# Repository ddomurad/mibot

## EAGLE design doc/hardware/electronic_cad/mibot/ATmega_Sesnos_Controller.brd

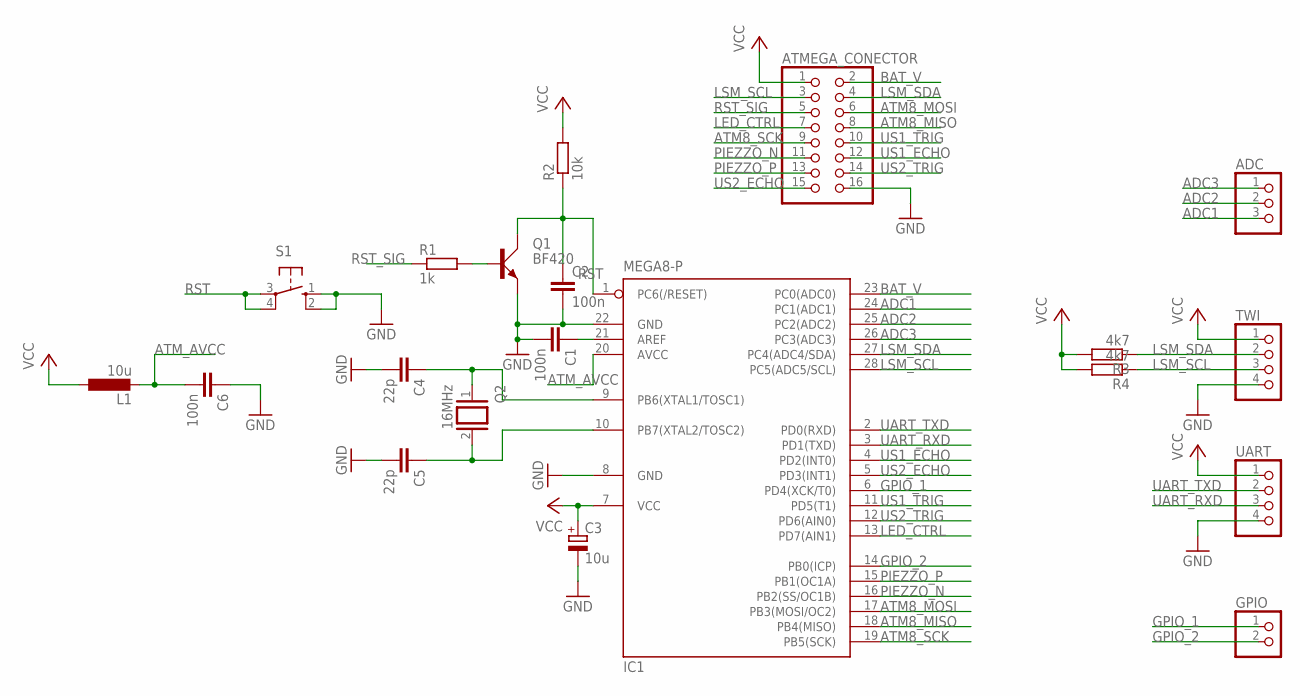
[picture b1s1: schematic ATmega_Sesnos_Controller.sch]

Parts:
ADC: PINHD-1X3/90; 1X03/90
ATMEGA_CONECTOR: PINHD-2X8; 2X08
C1, C2, C6: 100n; C025-024X044
C3: 10u; E5-5
C4, C5: 22p; C025-024X044
GPIO: PINHD-1X2/90; 1X02/90
IC1: MEGA8-P; DIL28-3
L1: 10u; 0204/7
Q1: BF420; SOT54D
Q2: 16MHz; QS
R1: 1k; 0309/10
R2: 10k; 0309/10
R3, R4: 4k7; 0204/5
S1: 10-XX; B3F-10XX
TWI: PINHD-1X4/90; 1X04/90
UART: PINHD-1X4/90; 1X04/90

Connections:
ADC1: ADC.3, IC1.24 (PC1(ADC1))
ADC2: ADC.2, IC1.25 (PC2(ADC2))
ADC3: ADC.1, IC1.26 (PC3(ADC3))
ATM8_MISO: ATMEGA_CONECTOR.8, IC1.18 (PB4(MISO))
ATM8_MOSI: ATMEGA_CONECTOR.6, IC1.17 (PB3(MOSI/OC2))
ATM8_SCK: ATMEGA_CONECTOR.9, IC1.19 (PB5(SCK))
ATM_AVCC: C6.2, IC1.20 (AVCC), L1.2
BAT_V: ATMEGA_CONECTOR.2, IC1.23 (PC0(ADC0))
GND: ATMEGA_CONECTOR.16, C1.2, C2.2, C3.-, C4.2, C5.2, C6.1, IC1.8 (GND), IC1.22 (GND), Q1.E, S1.1 (S), S1.2 (S1), TWI.4, UART.4
GPIO_1: GPIO.1, IC1.6 (PD4(XCK/T0))
GPIO_2: GPIO.2, IC1.14 (PB0(ICP))
LED_CTRL: ATMEGA_CONECTOR.7, IC1.13 (PD7(AIN1))
LSM_SCL: ATMEGA_CONECTOR.3, IC1.28 (PC5(ADC5/SCL)), R4.1, TWI.3
LSM_SDA: ATMEGA_CONECTOR.4, IC1.27 (PC4(ADC4/SDA)), R3.1, TWI.2
unnamed: C1.1, IC1.21 (AREF)
unnamed: C4.1, IC1.9 (PB6(XTAL1/TOSC1)), Q2.1
unnamed: C5.1, IC1.10 (PB7(XTAL2/TOSC2)), Q2.2
unnamed: Q1.B, R1.2
PIEZZO_N: ATMEGA_CONECTOR.11, IC1.16 (PB2(SS/OC1B))
PIEZZO_P: ATMEGA_CONECTOR.13, IC1.15 (PB1(OC1A))
RST: C2.1, IC1.1 (PC6(/RESET)), Q1.C, R2.1, S1.3, S1.4 (P1)
RST_SIG: ATMEGA_CONECTOR.5, R1.1
UART_RXD: IC1.3 (PD1(TXD)), UART.3
UART_TXD: IC1.2 (PD0(RXD)), UART.2
US1_ECHO: ATMEGA_CONECTOR.12, IC1.4 (PD2(INT0))
US1_TRIG: ATMEGA_CONECTOR.10, IC1.11 (PD5(T1))
US2_ECHO: ATMEGA_CONECTOR.15, IC1.5 (PD3(INT1))
US2_TRIG: ATMEGA_CONECTOR.14, IC1.12 (PD6(AIN0))
VCC: ATMEGA_CONECTOR.1, C3.+, IC1.7 (VCC), L1.1, R2.2, R3.2, R4.2, TWI.1, UART.1

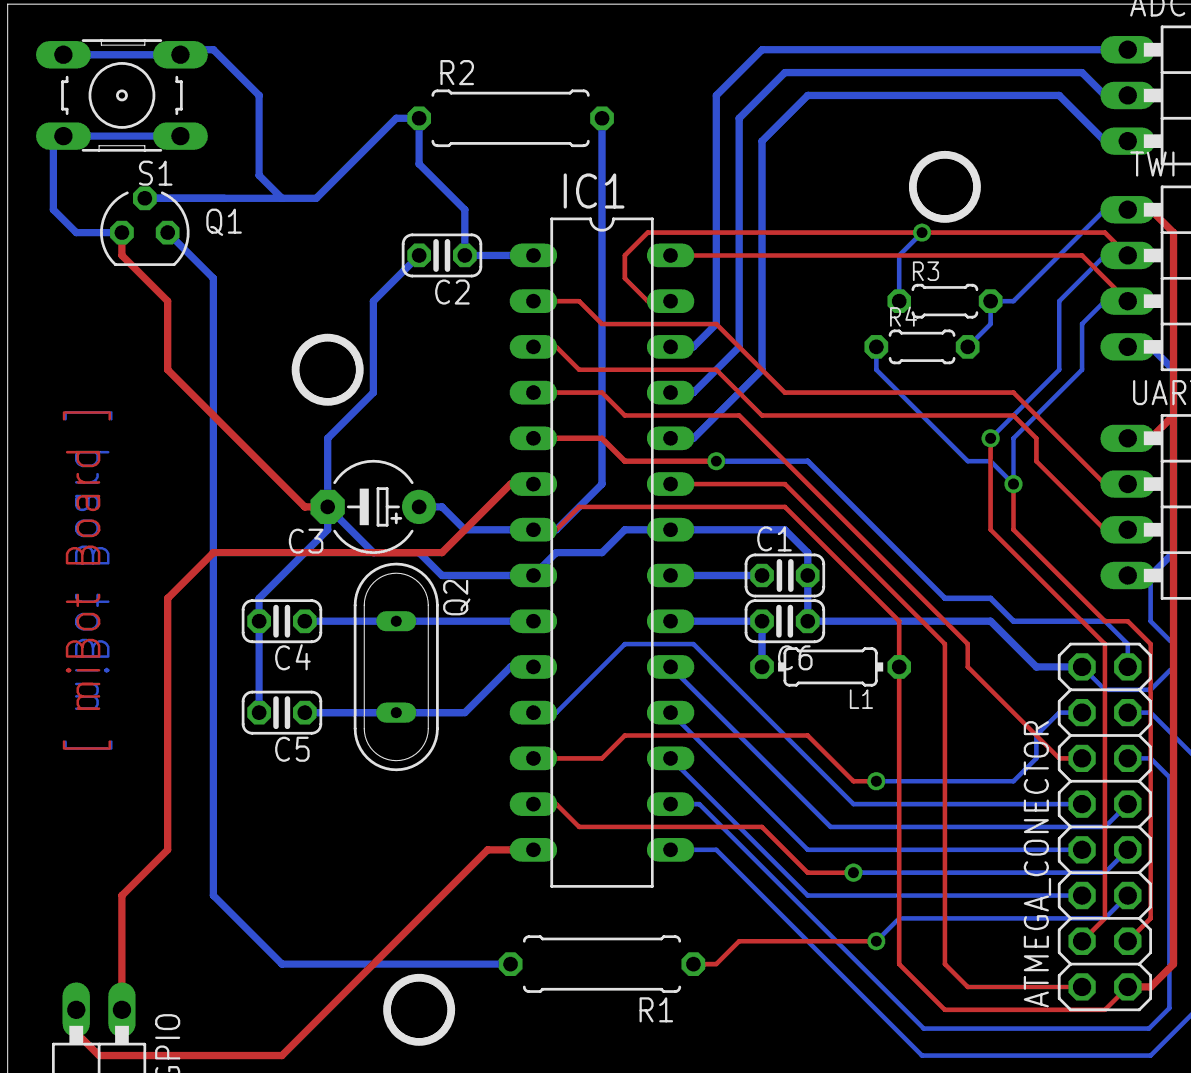
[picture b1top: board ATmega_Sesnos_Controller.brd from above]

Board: 2 copper layers, 20 parts (0 on the bottom side), 29 nets.

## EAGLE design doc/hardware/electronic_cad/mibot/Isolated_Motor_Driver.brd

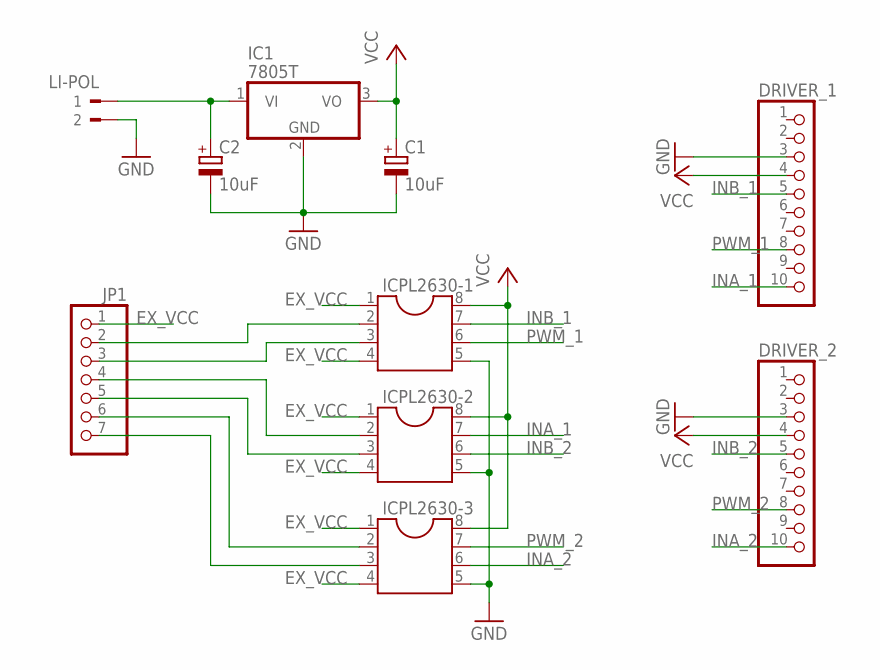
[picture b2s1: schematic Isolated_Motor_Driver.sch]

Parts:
C1, C2: 10uF; E5-5
DRIVER_1, DRIVER_2: PINHD-1X10; 1X10
IC1: 7805T; TO220H
ICPL2630-1, ICPL2630-2, ICPL2630-3: DIL8S; SOCKET-08
JP1: PINHD-1X7; 1X07
LI-POL: 90-2

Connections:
EX_INA_1: ICPL2630-1.2, JP1.2
EX_INA_2: ICPL2630-2.3, JP1.5
EX_INB_1: ICPL2630-1.3, JP1.3
EX_INB_2: ICPL2630-3.2, JP1.6
EX_PWM_1: ICPL2630-2.2, JP1.4
EX_PWM_2: ICPL2630-3.3, JP1.7
EX_VCC: ICPL2630-1.1, ICPL2630-1.4, ICPL2630-2.1, ICPL2630-2.4, ICPL2630-3.1, ICPL2630-3.4, JP1.1
GND: C1.-, C2.-, DRIVER_1.3, DRIVER_2.3, IC1.2 (GND), ICPL2630-1.5, ICPL2630-2.5, ICPL2630-3.5, LI-POL.2
INA_1: DRIVER_1.10, ICPL2630-2.7
INA_2: DRIVER_2.10, ICPL2630-3.6
INB_1: DRIVER_1.5, ICPL2630-1.7
INB_2: DRIVER_2.5, ICPL2630-2.6
unnamed: C2.+, IC1.1 (VI), LI-POL.1
PWM_1: DRIVER_1.8, ICPL2630-1.6
PWM_2: DRIVER_2.8, ICPL2630-3.7
VCC: C1.+, DRIVER_1.4, DRIVER_2.4, IC1.3 (VO), ICPL2630-1.8, ICPL2630-2.8, ICPL2630-3.8

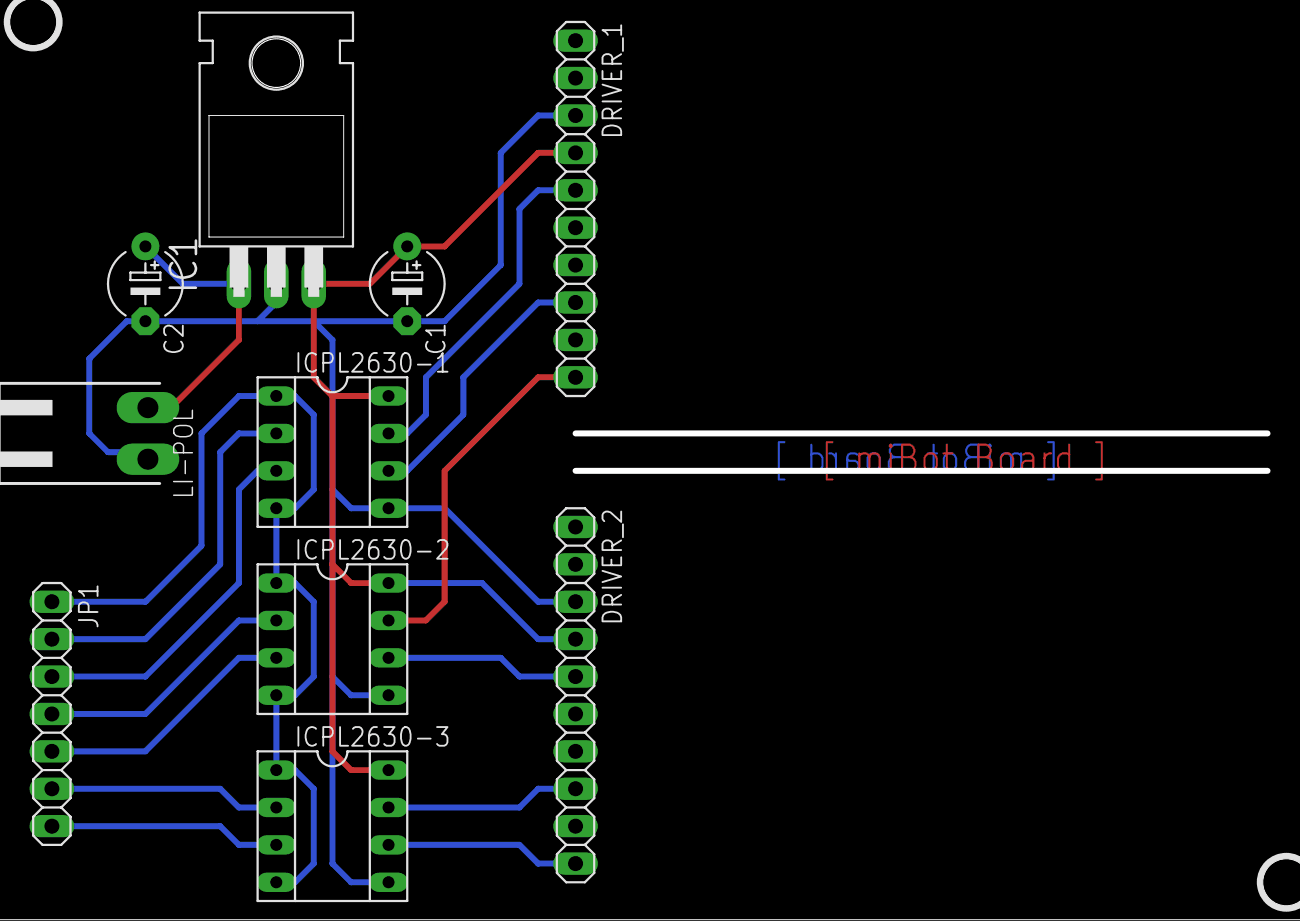
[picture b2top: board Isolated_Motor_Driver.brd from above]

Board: 2 copper layers, 10 parts (0 on the bottom side), 16 nets.

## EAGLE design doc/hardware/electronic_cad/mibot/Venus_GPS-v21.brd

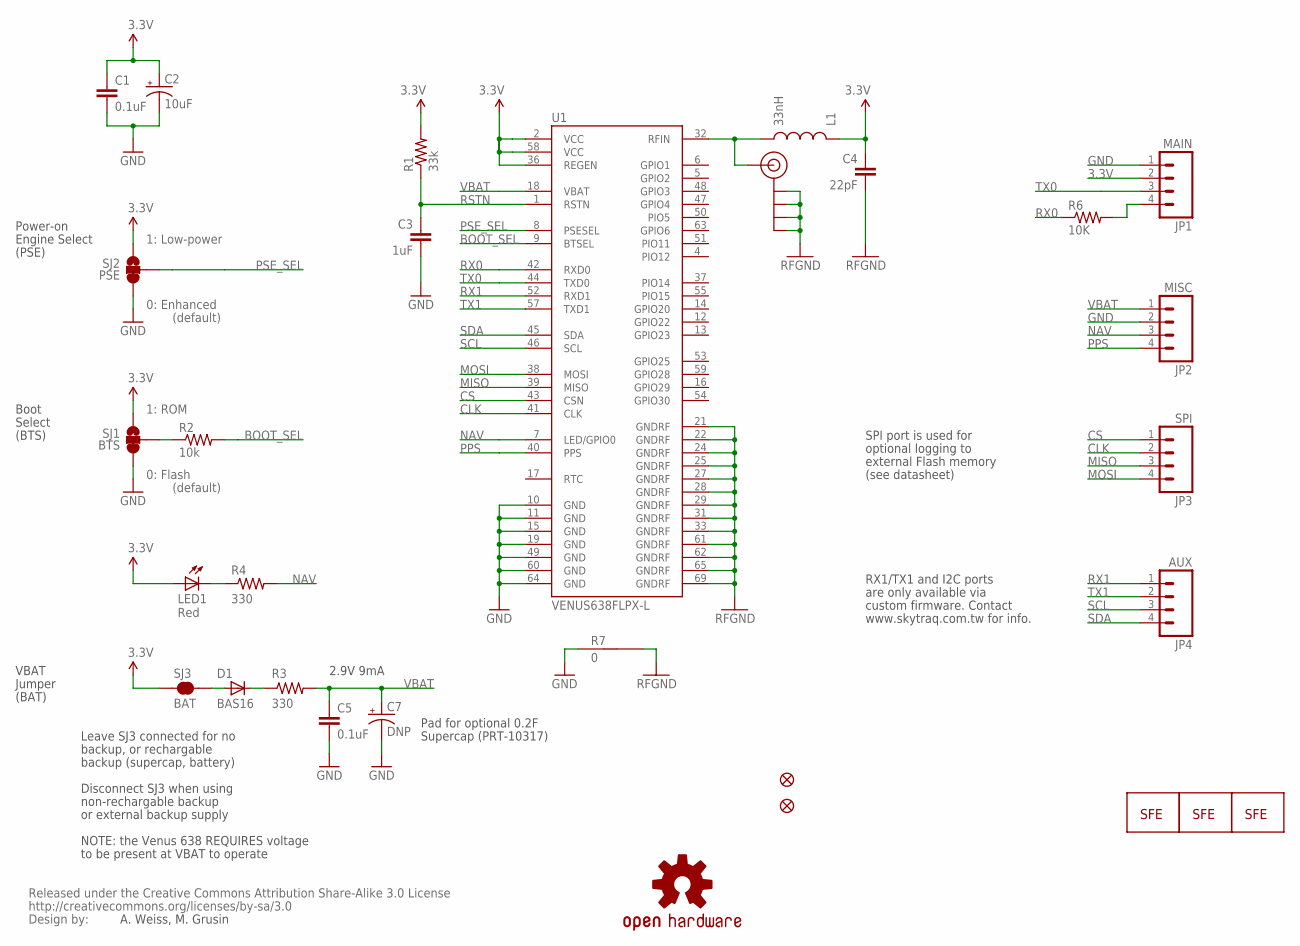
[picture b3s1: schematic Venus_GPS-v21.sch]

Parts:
C1, C5: 0.1uF; 0402-CAP
C2: 10uF; EIA3216
C3: 1uF; 0402-CAP
C4: 22pF; 0402-CAP
C7: DNP; EN_J2
D1: BAS16; SOD-323
JP1: MAIN; 1X04
JP2: MISC; 1X04
JP3: SPI; 1X04
JP4: AUX; 1X04
JP5: SMA_EDGE; SMA-EDGE
JP6, JP7: FIDUCIALUFIDUCIAL; MICRO-FIDUCIAL
L1: 33nH; C0402
LED1: Red; LED-0603
LOGO1, LOGO2: LOGO-SFESK; SFE-LOGO-FLAME
LOGO3: LOGO-SFENW2; SFE-NEW-WEB
R1: 33k; 0402-RES
R2: 10k; 0402-RES
R3, R4: 330; 0402-RES
R6: 10K; 0402-RES
R7: 0; GND-JUMP
SJ1: BTS; SJ_3_PASTE2&3
SJ2: PSE; SJ_3_PASTE2&3
SJ3: BAT; SJ_2S
U1: VENUS638FLPX-L; VENUS638FLPX
U$4: OSHW-LOGOS; OSHW-LOGO-S
U$5: CREATIVE_COMMONS

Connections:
3.3V: C1.1, C2.A (+), C4.1, JP1.2, L1.1, LED1.A, R1.2, SJ1.1, SJ2.1, SJ3.1, U1.2 (VCC), U1.36 (REGEN), U1.58 (VCC)
ANT: JP5.SIG (SIGNAL), L1.2, U1.32 (RFIN)
BOOT_SEL: R2.2, U1.9 (BTSEL)
CLK: JP3.2, U1.41 (CLK)
CS: JP3.1, U1.43 (CSN)
GND: C1.2, C2.C (-), C3.2, C5.2, C7.-, JP1.1, JP2.2, R7.1, SJ1.3, SJ2.3, U1.10 (GND), U1.11 (GND), U1.15 (GND), U1.19 (GND), U1.49 (GND), U1.60 (GND), U1.64 (GND)
MISO: JP3.3, U1.39 (MISO)
MOSI: JP3.4, U1.38 (MOSI)
unnamed: LED1.C, R4.1
unnamed: R2.1, SJ1.2
unnamed: D1.1 (C), R3.1
unnamed: D1.2 (A), SJ3.2
NAV: JP2.3, R4.2, U1.7 (LED/GPIO0)
PPS: JP2.4, U1.40 (PPS)
PSE_SEL: SJ2.2, U1.8 (PSESEL)
RFGND: C4.2, JP5.GND@0 (GND), JP5.GND@1 (GND), JP5.GND@2 (GND), JP5.GND@3 (GND), R7.2, U1.21 (GNDRF), U1.22 (GNDRF), U1.24 (GNDRF), U1.25 (GNDRF), U1.27 (GNDRF), U1.28 (GNDRF), U1.29 (GNDRF), U1.31 (GNDRF), U1.33 (GNDRF), U1.61 (GNDRF), U1.62 (GNDRF), U1.65 (GNDRF), U1.69 (GNDRF)
RSTN: C3.1, R1.1, U1.1 (RSTN)
RX0: R6.1, U1.42 (RXD0)
RX1: JP4.1, U1.52 (RXD1)
RX01: JP1.4, R6.2
SCL: JP4.3, U1.46 (SCL)
SDA: JP4.4, U1.45 (SDA)
TX0: JP1.3, U1.44 (TXD0)
TX1: JP4.2, U1.57 (TXD1)
VBAT: C5.1, C7.+, JP2.1, R3.2, U1.18 (VBAT)

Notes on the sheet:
RFGND
1: Low-power
0: Enhanced
0: Flash
1: ROM
(default)
A. Weiss, M. Grusin
Supercap (PRT-10317)
Pad for optional 0.2F
2.9V 9mA
RX1/TX1 and I2C ports
are only available via
SPI port is used for
optional logging to
external Flash memory
(see datasheet)
custom firmware. Contact
www.skytraq.com.tw for info.
Power-on
Engine Select
Boot
Select
(PSE)
(BTS)
VBAT
Jumper
(BAT)
Leave SJ3 connected for no
backup, or rechargable
backup (supercap, battery)
Disconnect SJ3 when using
non-rechargable backup
or external backup supply
NOTE: the Venus 638 REQUIRES voltage
to be present at VBAT to operate

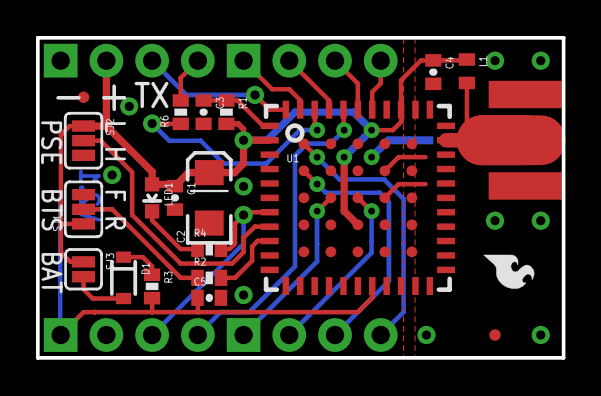
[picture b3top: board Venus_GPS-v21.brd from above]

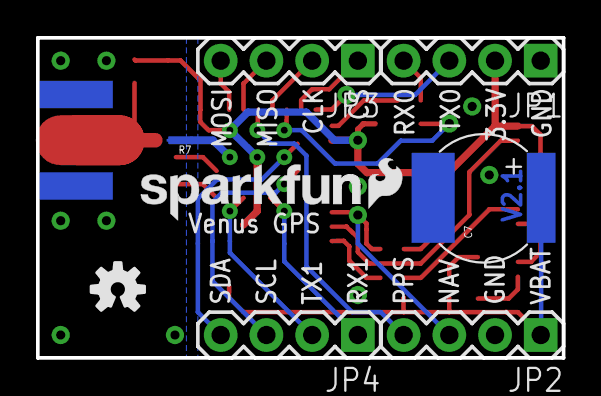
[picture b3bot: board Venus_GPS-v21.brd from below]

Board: 2 copper layers, 29.2 x 17.8 mm, 31 parts (9 on the bottom side), 25 nets.

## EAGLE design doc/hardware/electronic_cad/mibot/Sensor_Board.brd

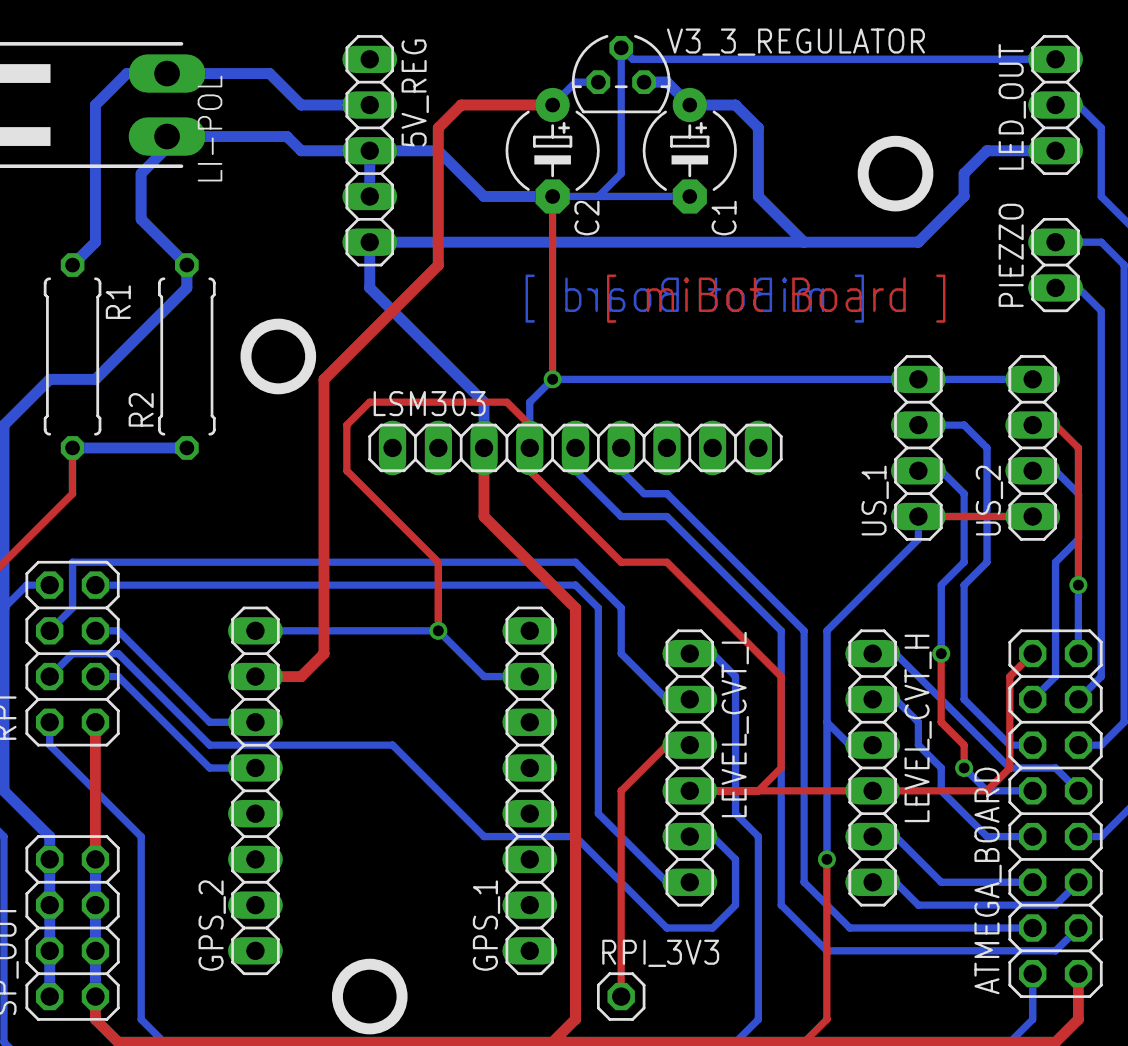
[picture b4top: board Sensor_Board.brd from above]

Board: 2 copper layers, 20 parts (0 on the bottom side), 25 nets.

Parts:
5V_REG: 1X05
ATMEGA_BOARD: 2X08
C1, C2: 10uF; E5-5
GPS_1, GPS_2: 1X08
LED_OUT: 1X03
LEVEL_CVT_H: 1X06
LEVEL_CVT_L: 1X06
LI-POL: 90-2
LSM303: 1X09
PIEZZO: 1X02
R1, R2: 1M; 0309/10
RPI: 2X04
RPI_3V3: 1X01
SP_OUT: 2X04
US_1, US_2: 1X04
V3_3_REGULATOR: TO92

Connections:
ATM8_MISO: ATMEGA_BOARD.8, LEVEL_CVT_H.2
ATM8_MOSI: ATMEGA_BOARD.6, LEVEL_CVT_H.5
ATM8_SCK: ATMEGA_BOARD.9, LEVEL_CVT_H.1
ATM_RST: ATMEGA_BOARD.5, LEVEL_CVT_H.6
BAT_V: ATMEGA_BOARD.2, R1.2, R2.1
GND: 5V_REG.3, 5V_REG.4, ATMEGA_BOARD.16, C1.-, C2.-, GPS_1.7, GPS_2.8, LED_OUT.3, LEVEL_CVT_H.4, LEVEL_CVT_L.4, LI-POL.2, LSM303.4, R2.2, RPI.8, SP_OUT.2, SP_OUT.4, SP_OUT.6, SP_OUT.8, US_1.4, US_2.4, V3_3_REGULATOR.2
GPS_RX: GPS_2.5, RPI.3
GPS_TX: GPS_2.6, RPI.5
LED_CTRL: ATMEGA_BOARD.7, LED_OUT.2
LSM_SCL: ATMEGA_BOARD.3, LSM303.5
LSM_SDA: ATMEGA_BOARD.4, LSM303.6
PIEZZO_N: ATMEGA_BOARD.11, PIEZZO.2
PIEZZO_P: ATMEGA_BOARD.13, PIEZZO.1
RPI_3V3: LEVEL_CVT_L.3, RPI_3V3.1
RPI_ATM_RST: LEVEL_CVT_L.6, RPI.7
RPI_MISO: LEVEL_CVT_L.2, RPI.6
RPI_MOSI: LEVEL_CVT_L.5, RPI.4
RPI_SCK: LEVEL_CVT_L.1, RPI.2
US1_ECHO: ATMEGA_BOARD.12, US_1.3
US1_TRIG: ATMEGA_BOARD.10, US_1.2
US2_ECHO: ATMEGA_BOARD.15, US_2.3
US2_TRIG: ATMEGA_BOARD.14, US_2.2
V3_3: C2.+, GPS_2.7, V3_3_REGULATOR.1
VCC: 5V_REG.5, ATMEGA_BOARD.1, C1.+, LED_OUT.1, LEVEL_CVT_H.3, LSM303.3, RPI.1, SP_OUT.1, SP_OUT.3, SP_OUT.5, SP_OUT.7, US_1.1, US_2.1, V3_3_REGULATOR.3
V_LI_POL: 5V_REG.2, LI-POL.1, R1.1

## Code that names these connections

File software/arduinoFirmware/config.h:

#ifndef __CONFIG_H
#define __CONFIG_H

#include "Arduino.h"
#include "HardwareSerial.h"

// configs
//#define ENABLE_TRACE
//#define ENABLE_TRACE2
//#define ENABLE_TRACE3

#define GSERIAL_BAUD 19200
#define GSERIAL &Serial

#define __ERROR_TIMER   1000

#define LSM_ACC_ADDR               0b0011000 //accelerometer address
#define LSM_ACC_CTRL_REG1_A_ADDR   0b00100000 //CTRL_REG1_A_ADDR
#define LSM_ACC_OUT_ADDR           0b10101000 //first output_register ( OUT_X_L_A )

#define LSM_ACC_PM    0x20 //normal mode
#define LSM_ACC_DR    0x00 //50 hz
#define LSM_ACC_XYZ   0x07 //enable x,y,z

#define LSM_MAG_ADDR       0b0011110//magnetometer address
#define LSM_MAG_CRA_REG_M_ADDR   0x00
#define LSM_MAG_CRB_REG_M_ADDR   0x01
#define LSM_MAG_MR_REG_M_ADDR    0x02
#define LSM_MAG_OUT_ADDR         0x03 //first output register (OUT_X_H_M)

#define LSM_MAG_DO    0x10 // 15 Hz
#define LSM_MAG_GN    0x20 // +- 1.3 
#define LSM_MAG_MD    0x00 //Continuos-sonverion mode

// post config
#define LSM_ACC_CTRL_REG1_A  ( LSM_ACC_PM | LSM_ACC_DR | LSM_ACC_XYZ )

#define LSM_MAG_CRA_REG_M ( LSM_MAG_DO )
#define LSM_MAG_CRB_REG_M ( LSM_MAG_GN )
#define LSM_MAG_MR_REG_M  ( LSM_MAG_MD )

#define US1_TRIG_PIN 53
#define US2_TRIG_PIN 52
#define US1_ECHO_PIN 51
#define US2_ECHO_PIN 50

#define US1_MAX_DISTANCE 200
#define US2_MAX_DISTANCE 200

#define PIEZZO_1_PIN 31
#define PIEZZO_2_PIN 30

#define MOTORS_LOCK_PIN 42
#endif

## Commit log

2015-03-06 some docs added
2015-03-07 Logger added
2015-03-07 Logger
2015-03-11 unit test lib added
2015-03-12 Some unit tests fixes and test results summary writen in python, html, css and js
2015-03-16 unit test mod, ssl server + logger' ;
2015-03-18 some changes
2015-03-18 backup added
2015-03-19 Logger moved to mibotUtils
2015-03-21 connection and server develop
2015-03-24 engines controller
2015-03-25 backup removed
2015-03-26 agg wiring pi
2015-03-27 diver controller
2015-03-27 add rpi build script
2015-03-27 drive model braking fix
2015-03-27 add log
2015-03-27 drive model added
2015-03-27 diver model
2015-03-28 pwm test
2015-03-28 test
2015-03-28 gpio fix
2015-03-28 drive model improvemend
2015-03-28 add utils .pro config
2015-03-29 client mod
2015-04-10 major changes
2015-04-10 source split
2015-04-10 add empty StatusStrategy
2015-04-10 compilation fix
2015-04-11 StatusReader added
2015-04-11 added StateReader
2015-04-14 mcp3004 setup fix
2015-04-15 log to file added
2015-04-15 file log fix
2015-04-15 add rebuild script
2015-04-16 Cpu status
2015-04-17 Cpu counter fix
2015-04-17 add memory status
2015-04-17 ram read bug fix;
2015-04-17 environment refresh
2015-04-23 add rpi init script
2015-04-24 build fix
2015-04-29 video streamer added
2015-05-14 TODO
2015-05-17 video streaming test
2015-05-18 VideoStreamProcess added
2015-05-18 video oprocess runner
2015-05-18 video stream process killer
2015-05-21 sime vide oclient added
2015-06-13 VideoStream final form
2015-06-13 Streamer messages fix
2015-07-02 big commit
2015-07-02 settings client and server
2015-07-02 ssl protocol version change
2015-07-03 ssl protocol change
2015-08-01 some sensor updates
2016-02-29 documents udpate
2016-03-03 building updated
2016-03-03 message
2016-03-03 sensors update
2016-03-03 sensors readgin performance fix
2016-03-03 desktop + fixes
2016-03-04 desktop client update + piezo ctrl
2016-03-04 piezo fix
2016-03-13 gps added and client major update
2016-03-20 builds fix
2016-03-20 video legacy compatibel
2016-04-10 udpate
2016-04-13 checkin
2016-04-16 time fix
2016-04-16 Acc simple calibration
2016-04-16 Acc calibration
2016-04-17 irr filter added
2016-04-17 add irr files
2016-04-23 auto pilot added
2016-04-23 autopilot client
2016-04-30 adds
2016-04-30 autopilot fix
2016-05-03 autopilot client update
2016-05-03 autopilot log fix
2016-08-20 cleanup
2016-08-20 update;
2016-08-27 desktop app udpate
2016-08-27 desktop update
2016-08-28 autopilot update
2016-08-30 das;
2016-09-01 autoi pilot tool update

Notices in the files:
parts and their libraries:
SparkFun: Released under the Creative Commons Attribution Share-Alike 3.0 License
SparkFun: http://creativecommons.org/licenses/by-sa/3.0
